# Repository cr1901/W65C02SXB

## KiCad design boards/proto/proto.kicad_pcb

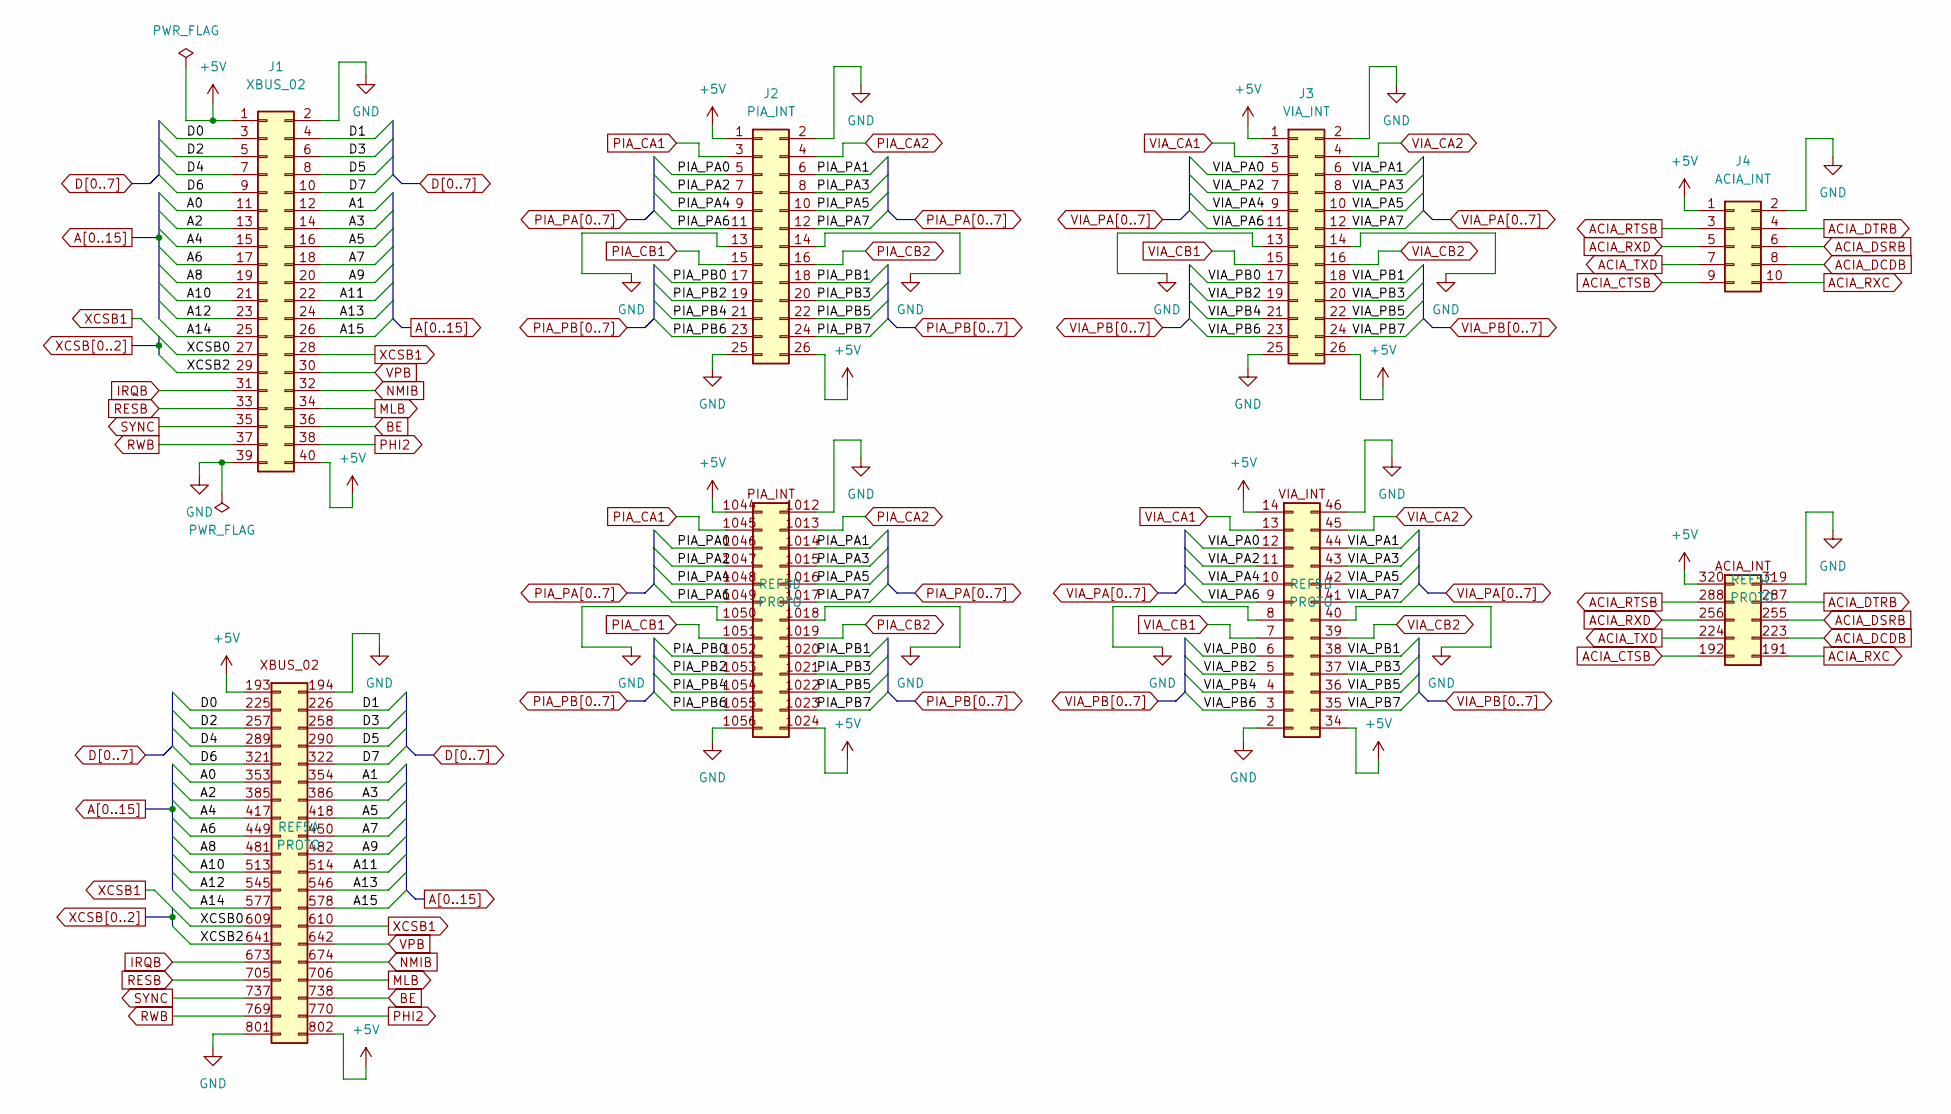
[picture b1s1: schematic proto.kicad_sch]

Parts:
J1: XBUS_02; PinSocket_2x20_P2.54mm_Vertical
J2: PIA_INT; PinSocket_2x13_P2.54mm_Vertical
J3: VIA_INT; PinSocket_2x13_P2.54mm_Vertical
J4: ACIA_INT; PinSocket_2x05_P2.54mm_Vertical
REF5: PROTO; Prototype Area

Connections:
+5V: J1.1, J1.40, J2.1, J2.26, J3.1, J3.26, J4.1, REF5.14 (Pin_1), REF5.34 (Pin_26), REF5.193 (Pin_1), REF5.320 (Pin_1), REF5.802 (Pin_40), REF5.1024 (Pin_26), REF5.1044 (Pin_1), REF5.1057, REF5.1058, REF5.1059, REF5.1060, REF5.1061, REF5.1062, REF5.1063, REF5.1064, REF5.1065, REF5.1066, REF5.1067, REF5.1068, REF5.1069, REF5.1070, REF5.1071, REF5.1072, REF5.1073, REF5.1074, REF5.1075, REF5.1076, REF5.1077, REF5.1078, REF5.1079, REF5.1080, REF5.1081, REF5.1082, REF5.1083, REF5.1084, REF5.1085, REF5.1086, REF5.1087, REF5.1088, REF5.1089, REF5.1090, REF5.1091, REF5.1092, REF5.1093, REF5.1094, REF5.1095, REF5.1096, REF5.1097, REF5.1098, REF5.1099, REF5.1100, REF5.1101, REF5.1102, REF5.1103, REF5.1104, REF5.1105, REF5.1106, REF5.1107, REF5.1108, REF5.1109, REF5.1110, REF5.1111, REF5.1112, REF5.1113, REF5.1114, REF5.1115, REF5.1116, REF5.1117, REF5.1118, REF5.1119, REF5.1120, REF5.1121, REF5.1122, REF5.1123, REF5.1124, REF5.1125, REF5.1126, REF5.1127, REF5.1128, REF5.1129, REF5.1130, REF5.1131, REF5.1132, REF5.1133, REF5.1134, REF5.1135, REF5.1136, REF5.1137, REF5.1138, REF5.1139, REF5.1140, REF5.1141, REF5.1142, REF5.1143, REF5.1144, REF5.1145, REF5.1146, REF5.1309, REF5.1310, REF5.1311, REF5.1312, REF5.1313, REF5.1314, REF5.1315, REF5.1316, REF5.1317, REF5.1318, REF5.1319, REF5.1320, REF5.1321, REF5.1322, REF5.1323, REF5.1324, REF5.1325, REF5.1326, REF5.1327, REF5.1328, REF5.1329, REF5.1330, REF5.1331, REF5.1332, REF5.1333, REF5.1334, REF5.1335, REF5.1336, REF5.1337, REF5.1338, REF5.1339, REF5.1340, REF5.1341, REF5.1342, REF5.1343, REF5.1344, REF5.1345, REF5.1346, REF5.1347, REF5.1348, REF5.1349, REF5.1350, REF5.1351, REF5.1352, REF5.1353, REF5.1354, REF5.1355, REF5.1356, REF5.1357, REF5.1358, REF5.1359, REF5.1360, REF5.1361, REF5.1362, REF5.1363, REF5.1364, REF5.1365, REF5.1366, REF5.1367, REF5.1368, REF5.1369, REF5.1370, REF5.1371, REF5.1372, REF5.1373, REF5.1374, REF5.1375, REF5.1376, REF5.1377, REF5.1378, REF5.1379, REF5.1380, REF5.1381, REF5.1382, REF5.1383, REF5.1384, REF5.1385, REF5.1386, REF5.1387, REF5.1388, REF5.1389, REF5.1390, REF5.1391, REF5.1392, REF5.1393, REF5.1394, REF5.1395, REF5.1396, REF5.1397, REF5.1398, REF5.1399, REF5.1400, REF5.1401, REF5.1402, REF5.1403, REF5.1404, REF5.1405, REF5.1406, REF5.1407, REF5.1408, REF5.1409, REF5.1410, REF5.1411, REF5.1412, REF5.1413, REF5.1414, REF5.1415, REF5.1416, REF5.1417, REF5.1418, REF5.1419, REF5.1420, REF5.1421, REF5.1422, REF5.1423, REF5.1424, REF5.1425, REF5.1426, REF5.1427, REF5.1428, REF5.1429, REF5.1430, REF5.1431, REF5.1432, REF5.1433, REF5.1434, REF5.1435, REF5.1436, REF5.1437, REF5.1438, REF5.1439, REF5.1440, REF5.1441, REF5.1442, REF5.1443, REF5.1444, REF5.1445, REF5.1446, REF5.1447, REF5.1448, REF5.1449, REF5.1450, REF5.1451, REF5.1452, REF5.1453, REF5.1454, REF5.1455, REF5.1456, REF5.1457, REF5.1458, REF5.1459, REF5.1460, REF5.1461, REF5.1462, REF5.1463, REF5.1464, REF5.1465, REF5.1466, REF5.1467, REF5.1468, REF5.1469, REF5.1470, REF5.1471, REF5.1472, REF5.1473, REF5.1474, REF5.1475, REF5.1476, REF5.1477, REF5.1478, REF5.1479, REF5.1480, REF5.1481, REF5.1482, REF5.1483, REF5.1484, REF5.1485, REF5.1486, REF5.1487, REF5.1488, REF5.1489, REF5.1490, REF5.1491, REF5.1492, REF5.1493, REF5.1494, REF5.1495, REF5.1496, REF5.1497, REF5.1498, REF5.1499, REF5.1500, REF5.1501, REF5.1502, REF5.1503, REF5.1504, REF5.1505, REF5.1506, REF5.1507, REF5.1508, REF5.1509, REF5.1510, REF5.1511, REF5.1512, REF5.1513, REF5.1514, REF5.1515, REF5.1516, REF5.1517, REF5.1518, REF5.1519, REF5.1520, REF5.1521, REF5.1522, REF5.1523, REF5.1524, REF5.1525, REF5.1526, REF5.1527, REF5.1528, REF5.1529, REF5.1530, REF5.1531, REF5.1532, REF5.1533, REF5.1534, REF5.1535, REF5.1536, REF5.1537, REF5.1538, REF5.1539, REF5.1540, REF5.1541, REF5.1542, REF5.1543, REF5.1544, REF5.1545, REF5.1546, REF5.1547, REF5.1548, REF5.1549, REF5.1550, REF5.1551, REF5.1552, REF5.1553, REF5.1554, REF5.1555, REF5.1556, REF5.1557, REF5.1558, REF5.1559, REF5.1560, REF5.1561, REF5.1562, REF5.1563, REF5.1564, REF5.1565, REF5.1566, REF5.1567, REF5.1568, REF5.1569, REF5.1570, REF5.1571, REF5.1572, REF5.1573, REF5.1574, REF5.1575, REF5.1576, REF5.1577, REF5.1578, REF5.1579, REF5.1580, REF5.1581, REF5.1582, REF5.1583, REF5.1584, REF5.1585, REF5.1586, REF5.1587, REF5.1588, REF5.1589, REF5.1590, REF5.1591, REF5.1592, REF5.1593, REF5.1594, REF5.1595, REF5.1596, REF5.1597, REF5.1598, REF5.1599, REF5.1600, REF5.1601, REF5.1602, REF5.1603, REF5.1604, REF5.1605, REF5.1606, REF5.1607, REF5.1608, REF5.1609, REF5.1610, REF5.1611, REF5.1612, REF5.1613, REF5.1614, REF5.1615, REF5.1616, REF5.1617, REF5.1618, REF5.1619, REF5.1620, REF5.1621, REF5.1622, REF5.1623, REF5.1624, REF5.1625, REF5.1626, REF5.1627, REF5.1628, REF5.1629, REF5.1630, REF5.1631, REF5.1632, REF5.1633, REF5.1634, REF5.1635, REF5.1636, REF5.1637, REF5.1638, REF5.1639, REF5.1640, REF5.1641, REF5.1642, REF5.1643, REF5.1644, REF5.1645, REF5.1646, REF5.1647, REF5.1648, REF5.1649, REF5.1650
A0: J1.11, REF5.353 (Pin_11)
A1: J1.12, REF5.354 (Pin_12)
A2: J1.13, REF5.385 (Pin_13)
A3: J1.14, REF5.386 (Pin_14)
A4: J1.15, REF5.417 (Pin_15)
A5: J1.16, REF5.418 (Pin_16)
A6: J1.17, REF5.449 (Pin_17)
A7: J1.18, REF5.450 (Pin_18)
A8: J1.19, REF5.481 (Pin_19)
A9: J1.20, REF5.482 (Pin_20)
A10: J1.21, REF5.513 (Pin_21)
A11: J1.22, REF5.514 (Pin_22)
A12: J1.23, REF5.545 (Pin_23)
A13: J1.24, REF5.546 (Pin_24)
A14: J1.25, REF5.577 (Pin_25)
A15: J1.26, REF5.578 (Pin_26)
ACIA_CTSB: J4.9, REF5.192 (Pin_9)
ACIA_DCDB: J4.8, REF5.223 (Pin_8)
ACIA_DSRB: J4.6, REF5.255 (Pin_6)
ACIA_DTRB: J4.4, REF5.287 (Pin_4)
ACIA_RTSB: J4.3, REF5.288 (Pin_3)
ACIA_RXC: J4.10, REF5.191 (Pin_10)
ACIA_RXD: J4.5, REF5.256 (Pin_5)
ACIA_TXD: J4.7, REF5.224 (Pin_7)
BE: J1.36, REF5.738 (Pin_36)
D0: J1.3, REF5.225 (Pin_3)
D1: J1.4, REF5.226 (Pin_4)
D2: J1.5, REF5.257 (Pin_5)
D3: J1.6, REF5.258 (Pin_6)
D4: J1.7, REF5.289 (Pin_7)
D5: J1.8, REF5.290 (Pin_8)
D6: J1.9, REF5.321 (Pin_9)
D7: J1.10, REF5.322 (Pin_10)
GND: J1.2, J1.39, J2.2, J2.13, J2.14, J2.25, J3.2, J3.13, J3.14, J3.25, J4.2, REF5.2 (Pin_25), REF5.8 (Pin_13), REF5.40 (Pin_14), REF5.46 (Pin_2), REF5.194 (Pin_2), REF5.319 (Pin_2), REF5.801 (Pin_39), REF5.1012 (Pin_2), REF5.1018 (Pin_14), REF5.1050 (Pin_13), REF5.1056 (Pin_25), REF5.1147, REF5.1148, REF5.1149, REF5.1150, REF5.1151, REF5.1152, REF5.1153, REF5.1154, REF5.1155, REF5.1156, REF5.1157, REF5.1158, REF5.1159, REF5.1160, REF5.1161, REF5.1162, REF5.1163, REF5.1164, REF5.1165, REF5.1166, REF5.1167, REF5.1168, REF5.1169, REF5.1170, REF5.1171, REF5.1172, REF5.1173, REF5.1174, REF5.1175, REF5.1176, REF5.1177, REF5.1178, REF5.1179, REF5.1180, REF5.1181, REF5.1182, REF5.1183, REF5.1184, REF5.1185, REF5.1186, REF5.1187, REF5.1188, REF5.1189, REF5.1190, REF5.1191, REF5.1192, REF5.1193, REF5.1194, REF5.1195, REF5.1196, REF5.1197, REF5.1198, REF5.1199, REF5.1200, REF5.1201, REF5.1202, REF5.1203, REF5.1204, REF5.1205, REF5.1206, REF5.1207, REF5.1208, REF5.1209, REF5.1210, REF5.1211, REF5.1212, REF5.1213, REF5.1214, REF5.1215, REF5.1216, REF5.1217, REF5.1218, REF5.1219, REF5.1220, REF5.1221, REF5.1222, REF5.1223, REF5.1224, REF5.1225, REF5.1226, REF5.1227, REF5.1651, REF5.1652, REF5.1653, REF5.1654, REF5.1655, REF5.1656, REF5.1657, REF5.1658, REF5.1659, REF5.1660, REF5.1661, REF5.1662, REF5.1663, REF5.1664, REF5.1665, REF5.1666, REF5.1667, REF5.1668, REF5.1669, REF5.1670, REF5.1671, REF5.1672, REF5.1673, REF5.1674, REF5.1675, REF5.1676, REF5.1677, REF5.1678, REF5.1679, REF5.1680, REF5.1681, REF5.1682, REF5.1683, REF5.1684, REF5.1685, REF5.1686, REF5.1687, REF5.1688, REF5.1689, REF5.1690, REF5.1691, REF5.1692, REF5.1693, REF5.1694, REF5.1695, REF5.1696, REF5.1697, REF5.1698, REF5.1699, REF5.1700, REF5.1701, REF5.1702, REF5.1703, REF5.1704, REF5.1705, REF5.1706, REF5.1707, REF5.1708, REF5.1709, REF5.1710, REF5.1711, REF5.1712, REF5.1713, REF5.1714, REF5.1715, REF5.1716, REF5.1717, REF5.1718, REF5.1719, REF5.1720, REF5.1721, REF5.1722, REF5.1723, REF5.1724, REF5.1725, REF5.1726, REF5.1727, REF5.1728, REF5.1729, REF5.1730, REF5.1731, REF5.1732, REF5.1733, REF5.1734, REF5.1735, REF5.1736, REF5.1737, REF5.1738, REF5.1739, REF5.1740, REF5.1741, REF5.1742, REF5.1743, REF5.1744, REF5.1745, REF5.1746, REF5.1747, REF5.1748, REF5.1749, REF5.1750, REF5.1751, REF5.1752, REF5.1753, REF5.1754, REF5.1755, REF5.1756, REF5.1757, REF5.1758, REF5.1759, REF5.1760, REF5.1761, REF5.1762, REF5.1763, REF5.1764, REF5.1765, REF5.1766, REF5.1767, REF5.1768, REF5.1769, REF5.1770, REF5.1771, REF5.1772, REF5.1773, REF5.1774, REF5.1775, REF5.1776, REF5.1777, REF5.1778, REF5.1779, REF5.1780, REF5.1781, REF5.1782, REF5.1783, REF5.1784, REF5.1785, REF5.1786, REF5.1787, REF5.1788, REF5.1789, REF5.1790, REF5.1791, REF5.1792, REF5.1793, REF5.1794, REF5.1795, REF5.1796, REF5.1797, REF5.1798, REF5.1799, REF5.1800, REF5.1801, REF5.1802, REF5.1803, REF5.1804, REF5.1805, REF5.1806, REF5.1807, REF5.1808, REF5.1809, REF5.1810, REF5.1811, REF5.1812, REF5.1813, REF5.1814, REF5.1815, REF5.1816, REF5.1817, REF5.1818, REF5.1819, REF5.1820, REF5.1821, REF5.1822, REF5.1823, REF5.1824, REF5.1825, REF5.1826, REF5.1827, REF5.1828, REF5.1829, REF5.1830, REF5.1831, REF5.1832, REF5.1833, REF5.1834, REF5.1835, REF5.1836, REF5.1837, REF5.1838, REF5.1839, REF5.1840, REF5.1841, REF5.1842, REF5.1843, REF5.1844, REF5.1845, REF5.1846, REF5.1847, REF5.1848, REF5.1849, REF5.1850, REF5.1851, REF5.1852, REF5.1853, REF5.1854, REF5.1855, REF5.1856, REF5.1857, REF5.1858, REF5.1859, REF5.1860, REF5.1861, REF5.1862, REF5.1863, REF5.1864, REF5.1865, REF5.1866, REF5.1867, REF5.1868, REF5.1869, REF5.1870, REF5.1871, REF5.1872, REF5.1873, REF5.1874, REF5.1875, REF5.1876, REF5.1877, REF5.1878, REF5.1879, REF5.1880, REF5.1881, REF5.1882, REF5.1883, REF5.1884, REF5.1885, REF5.1886, REF5.1887, REF5.1888, REF5.1889, REF5.1890, REF5.1891, REF5.1892, REF5.1893, REF5.1894, REF5.1895, REF5.1896, REF5.1897, REF5.1898, REF5.1899, REF5.1900, REF5.1901, REF5.1902, REF5.1903, REF5.1904, REF5.1905, REF5.1906, REF5.1907, REF5.1908, REF5.1909, REF5.1910, REF5.1911, REF5.1912, REF5.1913, REF5.1914, REF5.1915, REF5.1916, REF5.1917, REF5.1918, REF5.1919, REF5.1920, REF5.1921, REF5.1922, REF5.1923, REF5.1924, REF5.1925, REF5.1926, REF5.1927, REF5.1928, REF5.1929, REF5.1930, REF5.1931, REF5.1932, REF5.1933, REF5.1934, REF5.1935, REF5.1936, REF5.1937, REF5.1938, REF5.1939, REF5.1940, REF5.1941, REF5.1942, REF5.1943, REF5.1944, REF5.1945, REF5.1946, REF5.1947, REF5.1948, REF5.1949, REF5.1950, REF5.1951, REF5.1952, REF5.1953, REF5.1954, REF5.1955, REF5.1956, REF5.1957, REF5.1958, REF5.1959, REF5.1960, REF5.1961, REF5.1962, REF5.1963, REF5.1964, REF5.1965, REF5.1966, REF5.1967, REF5.1968, REF5.1969, REF5.1970, REF5.1971, REF5.1972, REF5.1973, REF5.1974, REF5.1975, REF5.1976, REF5.1977, REF5.1978, REF5.1979, REF5.1980, REF5.1981, REF5.1982, REF5.1983
IRQB: J1.31, REF5.673 (Pin_31)
MLB: J1.34, REF5.706 (Pin_34)
NMIB: J1.32, REF5.674 (Pin_32)
PHI2: J1.38, REF5.770 (Pin_38)
PIA_CA1: J2.3, REF5.1045 (Pin_3)
PIA_CA2: J2.4, REF5.1013 (Pin_4)
PIA_CB1: J2.15, REF5.1051 (Pin_15)
PIA_CB2: J2.16, REF5.1019 (Pin_16)
PIA_PA0: J2.5, REF5.1046 (Pin_5)
PIA_PA1: J2.6, REF5.1014 (Pin_6)
PIA_PA2: J2.7, REF5.1047 (Pin_7)
PIA_PA3: J2.8, REF5.1015 (Pin_8)
PIA_PA4: J2.9, REF5.1048 (Pin_9)
PIA_PA5: J2.10, REF5.1016 (Pin_10)
PIA_PA6: J2.11, REF5.1049 (Pin_11)
PIA_PA7: J2.12, REF5.1017 (Pin_12)
PIA_PB0: J2.17, REF5.1052 (Pin_17)
PIA_PB1: J2.18, REF5.1020 (Pin_18)
PIA_PB2: J2.19, REF5.1053 (Pin_19)
PIA_PB3: J2.20, REF5.1021 (Pin_20)
PIA_PB4: J2.21, REF5.1054 (Pin_21)
PIA_PB5: J2.22, REF5.1022 (Pin_22)
PIA_PB6: J2.23, REF5.1055 (Pin_23)
PIA_PB7: J2.24, REF5.1023 (Pin_24)
RESB: J1.33, REF5.705 (Pin_33)
RWB: J1.37, REF5.769 (Pin_37)
SYNC: J1.35, REF5.737 (Pin_35)
USER_RAIL: REF5.1228, REF5.1229, REF5.1230, REF5.1231, REF5.1232, REF5.1233, REF5.1234, REF5.1235, REF5.1236, REF5.1237, REF5.1238, REF5.1239, REF5.1240, REF5.1241, REF5.1242, REF5.1243, REF5.1244, REF5.1245, REF5.1246, REF5.1247, REF5.1248, REF5.1249, REF5.1250, REF5.1251, REF5.1252, REF5.1253, REF5.1254, REF5.1255, REF5.1256, REF5.1257, REF5.1258, REF5.1259, REF5.1260, REF5.1261, REF5.1262, REF5.1263, REF5.1264, REF5.1265, REF5.1266, REF5.1267, REF5.1268, REF5.1269, REF5.1270, REF5.1271, REF5.1272, REF5.1273, REF5.1274, REF5.1275, REF5.1276, REF5.1277, REF5.1278, REF5.1279, REF5.1280, REF5.1281, REF5.1282, REF5.1283, REF5.1284, REF5.1285, REF5.1286, REF5.1287, REF5.1288, REF5.1289, REF5.1290, REF5.1291, REF5.1292, REF5.1293, REF5.1294, REF5.1295, REF5.1296, REF5.1297, REF5.1298, REF5.1299, REF5.1300, REF5.1301, REF5.1302, REF5.1303, REF5.1304, REF5.1305, REF5.1306, REF5.1307, REF5.1308, REF5.1984, REF5.1985, REF5.1986, REF5.1987, REF5.1988, REF5.1989, REF5.1990, REF5.1991, REF5.1992, REF5.1993, REF5.1994, REF5.1995, REF5.1996, REF5.1997, REF5.1998, REF5.1999, REF5.2000, REF5.2001, REF5.2002, REF5.2003, REF5.2004, REF5.2005, REF5.2006, REF5.2007, REF5.2008, REF5.2009, REF5.2010, REF5.2011, REF5.2012, REF5.2013, REF5.2014, REF5.2015, REF5.2016, REF5.2017, REF5.2018, REF5.2019, REF5.2020, REF5.2021, REF5.2022, REF5.2023, REF5.2024, REF5.2025, REF5.2026, REF5.2027, REF5.2028, REF5.2029, REF5.2030, REF5.2031, REF5.2032, REF5.2033, REF5.2034, REF5.2035, REF5.2036, REF5.2037, REF5.2038, REF5.2039, REF5.2040, REF5.2041, REF5.2042, REF5.2043, REF5.2044, REF5.2045, REF5.2046, REF5.2047, REF5.2048, REF5.2049, REF5.2050, REF5.2051, REF5.2052, REF5.2053, REF5.2054, REF5.2055, REF5.2056, REF5.2057, REF5.2058, REF5.2059, REF5.2060, REF5.2061, REF5.2062, REF5.2063, REF5.2064, REF5.2065, REF5.2066, REF5.2067, REF5.2068, REF5.2069, REF5.2070, REF5.2071, REF5.2072, REF5.2073, REF5.2074, REF5.2075, REF5.2076, REF5.2077, REF5.2078, REF5.2079, REF5.2080, REF5.2081, REF5.2082, REF5.2083, REF5.2084, REF5.2085, REF5.2086, REF5.2087, REF5.2088, REF5.2089, REF5.2090, REF5.2091, REF5.2092, REF5.2093, REF5.2094, REF5.2095, REF5.2096, REF5.2097, REF5.2098, REF5.2099, REF5.2100, REF5.2101, REF5.2102, REF5.2103, REF5.2104, REF5.2105, REF5.2106, REF5.2107, REF5.2108, REF5.2109, REF5.2110, REF5.2111, REF5.2112, REF5.2113, REF5.2114, REF5.2115, REF5.2116, REF5.2117, REF5.2118, REF5.2119, REF5.2120, REF5.2121, REF5.2122, REF5.2123, REF5.2124, REF5.2125, REF5.2126, REF5.2127, REF5.2128, REF5.2129, REF5.2130, REF5.2131, REF5.2132, REF5.2133, REF5.2134, REF5.2135, REF5.2136, REF5.2137, REF5.2138, REF5.2139, REF5.2140, REF5.2141, REF5.2142, REF5.2143, REF5.2144, REF5.2145, REF5.2146, REF5.2147, REF5.2148, REF5.2149, REF5.2150, REF5.2151, REF5.2152, REF5.2153, REF5.2154, REF5.2155, REF5.2156, REF5.2157, REF5.2158, REF5.2159, REF5.2160, REF5.2161, REF5.2162, REF5.2163, REF5.2164, REF5.2165, REF5.2166, REF5.2167, REF5.2168, REF5.2169, REF5.2170, REF5.2171, REF5.2172, REF5.2173, REF5.2174, REF5.2175, REF5.2176, REF5.2177, REF5.2178, REF5.2179, REF5.2180, REF5.2181, REF5.2182, REF5.2183, REF5.2184, REF5.2185, REF5.2186, REF5.2187, REF5.2188, REF5.2189, REF5.2190, REF5.2191, REF5.2192, REF5.2193, REF5.2194, REF5.2195, REF5.2196, REF5.2197, REF5.2198, REF5.2199, REF5.2200, REF5.2201, REF5.2202, REF5.2203, REF5.2204, REF5.2205, REF5.2206, REF5.2207, REF5.2208, REF5.2209, REF5.2210, REF5.2211, REF5.2212, REF5.2213, REF5.2214, REF5.2215, REF5.2216, REF5.2217, REF5.2218, REF5.2219, REF5.2220, REF5.2221, REF5.2222, REF5.2223, REF5.2224, REF5.2225, REF5.2226, REF5.2227, REF5.2228, REF5.2229, REF5.2230, REF5.2231, REF5.2232, REF5.2233, REF5.2234, REF5.2235, REF5.2236, REF5.2237, REF5.2238, REF5.2239, REF5.2240, REF5.2241, REF5.2242, REF5.2243, REF5.2244, REF5.2245, REF5.2246, REF5.2247, REF5.2248, REF5.2249, REF5.2250, REF5.2251, REF5.2252, REF5.2253, REF5.2254, REF5.2255, REF5.2256, REF5.2257, REF5.2258, REF5.2259, REF5.2260, REF5.2261, REF5.2262, REF5.2263, REF5.2264, REF5.2265, REF5.2266, REF5.2267, REF5.2268, REF5.2269, REF5.2270, REF5.2271, REF5.2272, REF5.2273, REF5.2274, REF5.2275, REF5.2276, REF5.2277, REF5.2278, REF5.2279, REF5.2280, REF5.2281, REF5.2282, REF5.2283, REF5.2284, REF5.2285, REF5.2286, REF5.2287, REF5.2288, REF5.2289, REF5.2290, REF5.2291, REF5.2292, REF5.2293, REF5.2294, REF5.2295, REF5.2296, REF5.2297, REF5.2298, REF5.2299, REF5.2300, REF5.2301, REF5.2302, REF5.2303, REF5.2304, REF5.2305, REF5.2306, REF5.2307, REF5.2308, REF5.2309, REF5.2310, REF5.2311, REF5.2312, REF5.2313, REF5.2314, REF5.2315, REF5.2316
VIA_CA1: J3.3, REF5.13 (Pin_3)
VIA_CA2: J3.4, REF5.45 (Pin_4)
VIA_CB1: J3.15, REF5.7 (Pin_15)
VIA_CB2: J3.16, REF5.39 (Pin_16)
VIA_PA0: J3.5, REF5.12 (Pin_5)
VIA_PA1: J3.6, REF5.44 (Pin_6)
VIA_PA2: J3.7, REF5.11 (Pin_7)
VIA_PA3: J3.8, REF5.43 (Pin_8)
VIA_PA4: J3.9, REF5.10 (Pin_9)
VIA_PA5: J3.10, REF5.42 (Pin_10)
VIA_PA6: J3.11, REF5.9 (Pin_11)
VIA_PA7: J3.12, REF5.41 (Pin_12)
VIA_PB0: J3.17, REF5.6 (Pin_17)
VIA_PB1: J3.18, REF5.38 (Pin_18)
VIA_PB2: J3.19, REF5.5 (Pin_19)
VIA_PB3: J3.20, REF5.37 (Pin_20)
VIA_PB4: J3.21, REF5.4 (Pin_21)
VIA_PB5: J3.22, REF5.36 (Pin_22)
VIA_PB6: J3.23, REF5.3 (Pin_23)
VIA_PB7: J3.24, REF5.35 (Pin_24)
VPB: J1.30, REF5.642 (Pin_30)
XCSB0: J1.27, REF5.609 (Pin_27)
XCSB1: J1.28, REF5.610 (Pin_28)
XCSB2: J1.29, REF5.641 (Pin_29)

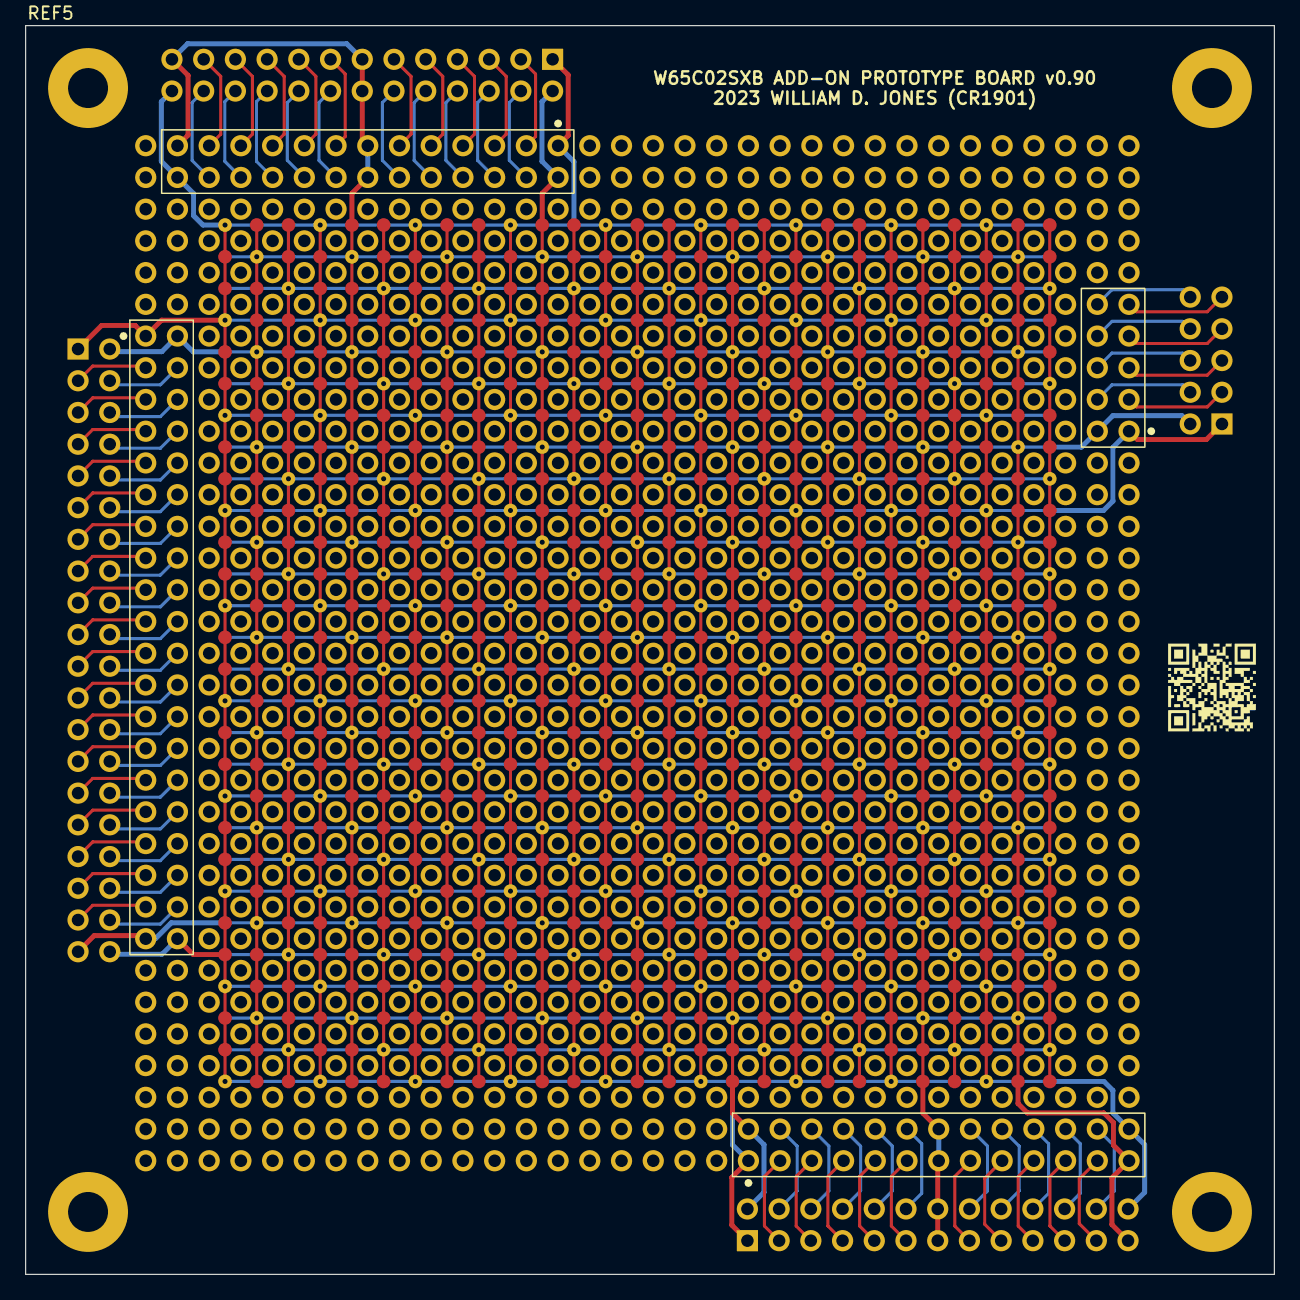
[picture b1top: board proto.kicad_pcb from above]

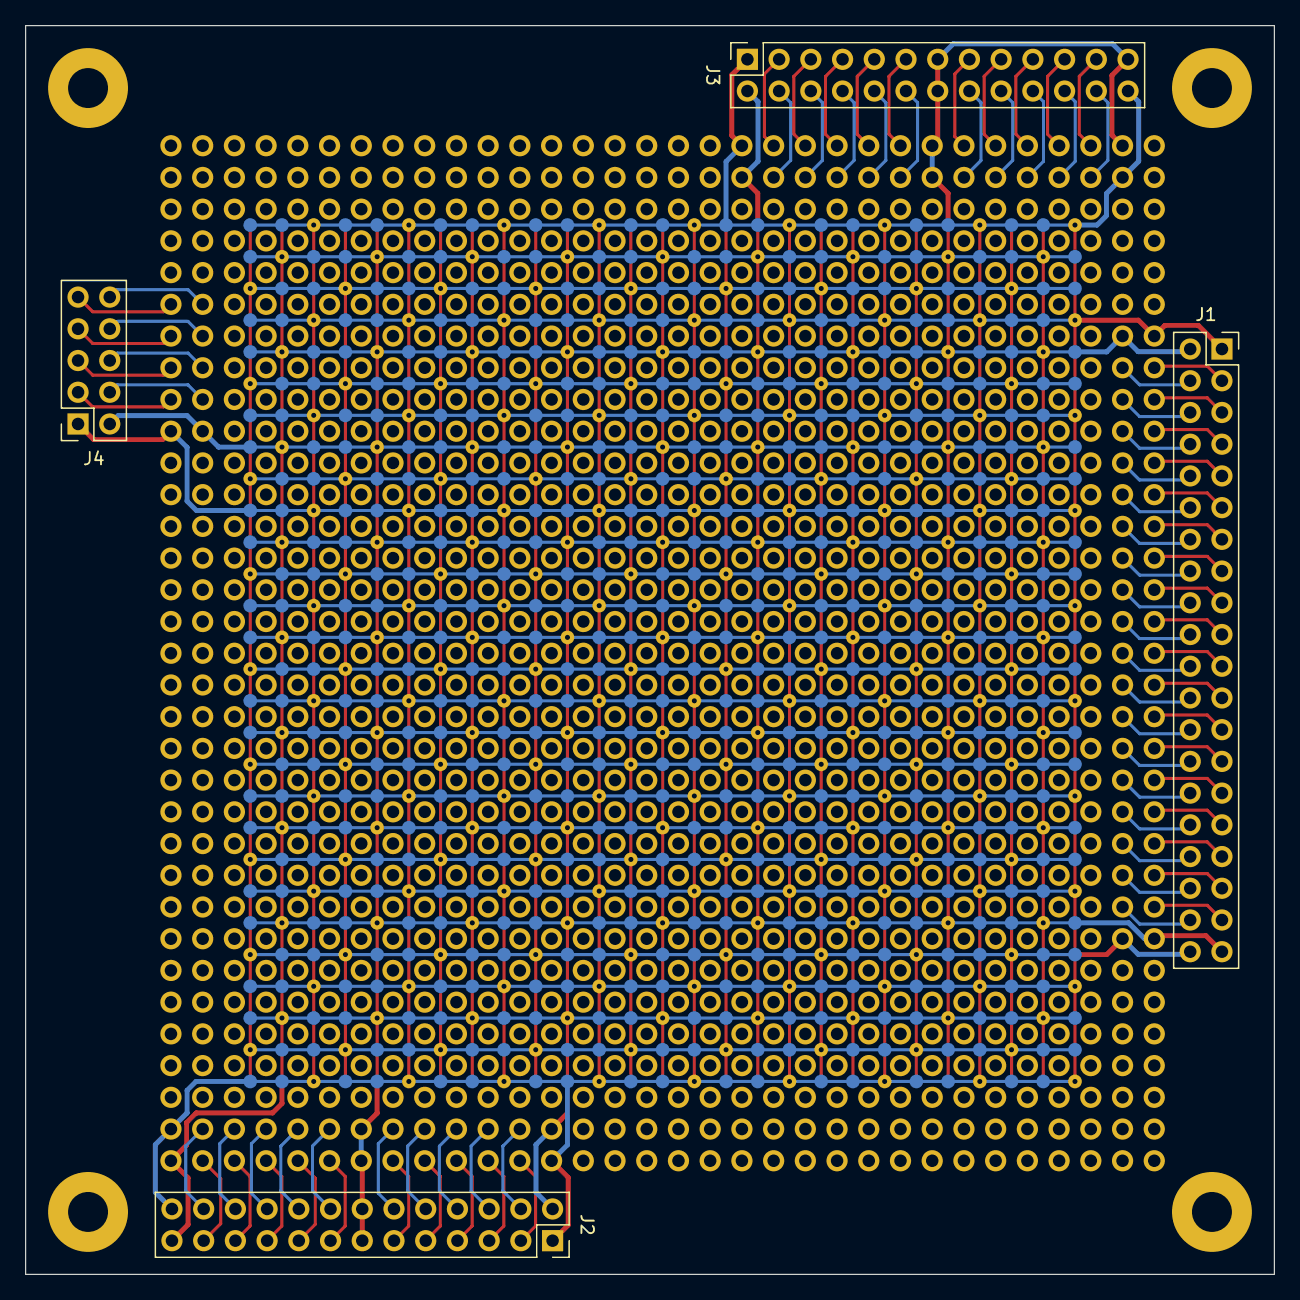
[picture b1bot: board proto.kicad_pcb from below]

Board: 2 copper layers, 100.0 x 100.0 mm, 9 parts (4 on the bottom side), 87 nets.

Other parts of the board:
REF6, REF7, REF8, REF9: MountingHole_3.2mm_M3_Pad

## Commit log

2023-07-27 Initial commit with programmer application and proof-of-concept hello binary.
2023-07-27 Trim unneeded features in programmer application.
2023-07-27 Make Makefile more generic.
2023-07-30 Fix loading vectors.
2023-07-30 Start interrupt-driven serial echo example. Transmit side working.
2023-07-30 Move IRQ out of serial.asm, use jump instead.
2023-07-30 Refactor IRQ more, add LD16 macro, give dead time for sending to test TX buffer drain.
2023-07-30 Optimize/correct documentation of serial routines.
2023-08-03 Add table-driven CRC examples.
2023-08-04 Add functions to print out CRC results to ACIA. Add stub serial RX functions.
2023-08-04 Add template Kicad PCB for making W65C02SXB expansion boards.
2023-08-08 Add start of prototype board.
2023-08-08 Create rough outline of Prototype Area (not numbered correctly).
2023-08-08 Remake Prototype area into central square to avoid renumbering manually.
2023-08-09 Create symbol for prototype area to break out connectors.
2023-08-09 Route header breakouts except power.
2023-08-09 Lay down vias and pads to break out power.
2023-08-09 Rework vias and pads to break out power.
2023-08-09 Add vias to bottom.
2023-08-09 Connect power traces across prototype board.
2023-08-10 Power traces were bad/disconnected. Incrementally redo them/add scripting.
2023-08-10 Redo and group power traces for hopefully the final time.
2023-08-10 Route PWR and GND traces from breakouts to proto rails.
2023-08-10 Completely routed design, except for user rail.
2023-08-10 Fix gerber output settings for PCB.
2023-08-11 Add a genproto.py script to automate generating a prototype area.
2023-08-11 Replace manual proto footprint with script-generated one (minus silkscreen).
2023-08-11 Add silkscreen directly to board footprint (easier coordinate system to work with).
2023-08-12 Modify genrails to completely autogenerate traces and nets, reroute destroyed tracks.
2023-08-12 Add missing rails.json config file.
2023-08-12 Finalize changes. Add silk text, mounting holes, silk QR code, silk orientation dots. Fix errant newline in genrails.py.
2023-08-12 Add JLCPCB design rules from https://gist.github.com/darkxst/f713268e5469645425eed40115fb8b49.
2023-08-12 Add QRCode footprint, add .gitignore for gerbers dir.
